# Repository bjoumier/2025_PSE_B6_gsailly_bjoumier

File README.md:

# 2025_PSE_B6_gsailly_bjoumier

### Choix Projet :

Dans le cadre de ce cours de Premier Système Embarqué, nous avons pour objectif de créer un système embarqué en ayant pour seule consigne d'y intégrer un AVR ATmega32u4 AT90USB1287 et une alimentation hybride :
- par un port USB, méthode utilisée pour la programmation, les tests et la configuration
- par une batterie Lithium, en mode autonome.

Notre binôme a donc choisi de réaliser une montre connectée qui a pour objectif principal d'afficher l'heure et de capturer les BPM de l'utilisateur. (D'autres fonctions pourront être ajoutées si elles sont réalisables)

---

### Réalisation Projet :

#### Partie Matériel :

Pour réaliser cette montre connectée, nous avons dans un premier temps utilisé le logiciel KiCad, pour réaliser le schéma et le PCB. *[(Voir /Materiel)](https://gitea.plil.fr/gsailly/2025_PSE_B6_gsailly_bjoumier/src/branch/main/Materiel)*

Suite à cette réalisation, nous avons :
- soudé le µC, le crystal et leurs capacités/résistances associées
- testé le bon fonctionnement de la carte via l'ICSP, (Comme nous n'avions pas encore le régulateur de tension et le cavalier, nous avons court-circuité la pate +5V du connecteur J8 avec R1 afin d'alimenter le µC)
- soudé les LEDs, puis testé ces dernières via un simple code pour les faire clignoter :

```c
	#define F_CPU 8000000UL
		
	#include <avr/io.h>
	#include <util/delay.h>
	
	void delay(volatile uint32_t nCount) {
	    while(nCount--) {}
	}
	
	int main(void) {
	
		CLKSEL0 = 0b00010101;   // sélection de l'horloge externe
		CLKSEL1 = 0b00001111;   // minimum de 8Mhz
		CLKPR = 0b10000000;     // modification du diviseur d'horloge (CLKPCE=1)
		CLKPR = 0;              // 0 pour pas de diviseur (diviseur de 1)
	
	    DDRB |= (1 << PB4) | (1 << PB5);
	
	    while(1) {
	         // LED sur PB5 ON
	        PORTB |= (1 << PB5);
	
	        // LED sur PB4 OFF
	        PORTB &= ~(1 << PB4);
	
	        _delay_ms(500);
	
	        // Inverser
	        PORTB &= ~(1 << PB5);
	        PORTB |= (1 << PB4);
	
	        _delay_ms(500);
	    }
	}
```
- soudé le capteur de BPM MAX30102 (que nous avons probablement grillé en le soudant puis en branchant la carte avant de souder le régulateur)
- soudé tous les connecteurs manquants ainsi que le régulateur de tension et l'inductance (ce qui nous a permis de brancher l'écran I2C et le module Bluetooth HC-05)

Enfin, à la dernière séance, nous avons soudé le MAX1811 qui nous a permis de faire fonctionner la montre via le chargeur LIPO en branchant la batterie.

#### Partie Logiciel :

Pour réaliser la partie logicielle de la montre, nous avons développé le programme embarqué en C pour le microcontrôleur ATmega32U4. *[(Voir /Logiciel)](https://gitea.plil.fr/gsailly/2025_PSE_B6_gsailly_bjoumier/src/branch/main/Logiciel)*

Nous avons utilisé plusieurs bibliothèques afin de faciliter la gestion des différents périphériques :

- **U8G2** : gestion de l’écran OLED SSD1306
- **LUFA** : gestion de la communication USB
- pilotes personnalisés pour :
  - le Bluetooth HC-05
  - le capteur MAX30102
  - l’I2C
  - les timers
  - la gestion de l’heure

##### Structure du projet

```text
Logiciel/
├──	montre_connectee/
│	├── include/
│	│   └── LUFA/
│	├── lib/
│	│   └── U8g2/
│	├── src/
│	│   ├── main.c
│	│   ├── display.c
│	│   ├── display.h
│	│   ├── i2c.c
│	│   ├── i2c.h
│	│   ├── max30102.c
│	│   ├── max30102.h
│	│   ├── timekeeper.c
│	│   ├── timekeeper.h
│	│   ├── timer.c
│	│   ├── timer.h
│	│   ├── uart.c
│	│   ├── uart.h
│	│   ├── usb_comm.c
│	│   └── usb_comm.h
│	└── Makefile
```

##### Fonctionnement général

Le programme initialise :
- l’écran OLED,
- la communication Bluetooth UART,
- les timers,
- la gestion du temps,
- ainsi que le capteur cardiaque MAX30102.

L’heure peut être synchronisée via Bluetooth grâce à l’application **Serial Bluetooth Terminal** sur tablette ou smartphone.

Un message au format suivant est envoyé :
```text
T14:30:00
```

Le microcontrôleur lit ensuite cette trame et met à jour l’horloge affichée à l’écran.

##### Affichage

L’écran affiche :
- l’heure actuelle,
- le rythme cardiaque en BPM (le capteur étant grillé, nous avons chois d'afficher une valeur de 80 BPM fixe),
- ainsi qu’une interface graphique réalisée avec la bibliothèque U8G2.

##### Communication Bluetooth

Le module **HC-05** communique avec l’ATmega32U4 via l’UART à 9600 bauds.

La réception Bluetooth est gérée directement dans la boucle principale du programme.

##### Capteur cardiaque

Le capteur **MAX30102** communique via le protocole I2C.

Nous avons développé un pilote permettant :
- l’initialisation du capteur,
- la lecture des valeurs IR,
- ainsi que le calcul du rythme cardiaque.

##### Compilation

Le projet est compilé avec `avr-gcc` via un `Makefile`.

Effacer :
```bash
make clean
```

Compilation :
```bash
make all
```

Appuer sur les boutons NHWB (maintenir) et RESET (1 pression) puis relâcher NHWB pour pouvoir re-flasher la carte.

Téléversement :
```bash
make upload
```

Débrancher puis Rebrancher la carte.

### Carte en fontionnement (USB et LIPO)

---

### Erreurs / Points d'amélioration :

#### Erreurs : 

- Mauvaise empreinte pour le crystal (empreinte légèrement trop petite).
- Nous avons voulu tester le capteur de BPM  avant d'avoir le régulateur de tension, ce qui a pu le griller (en plus de l'avoir soudé à une température trop élevée).

- Nous avions utilisé un mauvais baudrate (115200 au lieu de 9600), ce qui nous a fait perdre entre 30 et 45 minutes.
- Mauvais paramétrage de l'horloge qui prenait 8 secondes à réaliser une instruction d'1 seconde, ce qui nous a fait perdre entre 15 et 30 minutes. Nous avons résolu ce problème grâce aux 4 lignes de code fournies dans le cours de Mr Redon ainsi qu'en remplaçant le chiffre 16 (MHz) par 8 (MHz) dans le code ```uart.c``` : 

```c
CLKSEL0 = 0b00010101;   // sélection de l'horloge externe
CLKSEL1 = 0b00001111;   // minimum de 8Mhz
CLKPR = 0b10000000;     // modification du diviseur d'horloge (CLKPCE=1)
CLKPR = 0;              // 0 pour pas de diviseur (diviseur de 1)
```

```c
uint16_t ubrr = (F_CPU / 8 / baud) - 1;
```

#### Points d'amélioration :

- Utilisation d'un levier/interrupteur pour passer de l'alimentation USB à l'alimentaion sur batterie.
- Allumer la LED D4 qui indique le passage de la carte à l'alimentaion sur batterie.
- Ajouter des boutons sur la carte qui auraient permis de régler l'heure directement dessus (1 pression rajoute +1 à l'heure ou aux minutes ou aux secondes).
- Ajouter un sorte de "joystick" qui aurait pu servir à modifier l'heure (déplacement gauche pour reculer, déplacement droit pour avancer, déplacement haut pour passer à l'unité suivante, déplacement vers le bas pour passer à l'unité précédente).
- Ajouter une molette pour régler l'heure.

---

Premier Système Embarqué - IoT 3 - B6 - **[Notre Wiki](https://projets-se.plil.fr/mediawiki/index.php/SE3Groupe2025-6)** - *[Accès à notre machine de TP (zabeth16)](https://vnc.plil.fr/ssh/?16)*

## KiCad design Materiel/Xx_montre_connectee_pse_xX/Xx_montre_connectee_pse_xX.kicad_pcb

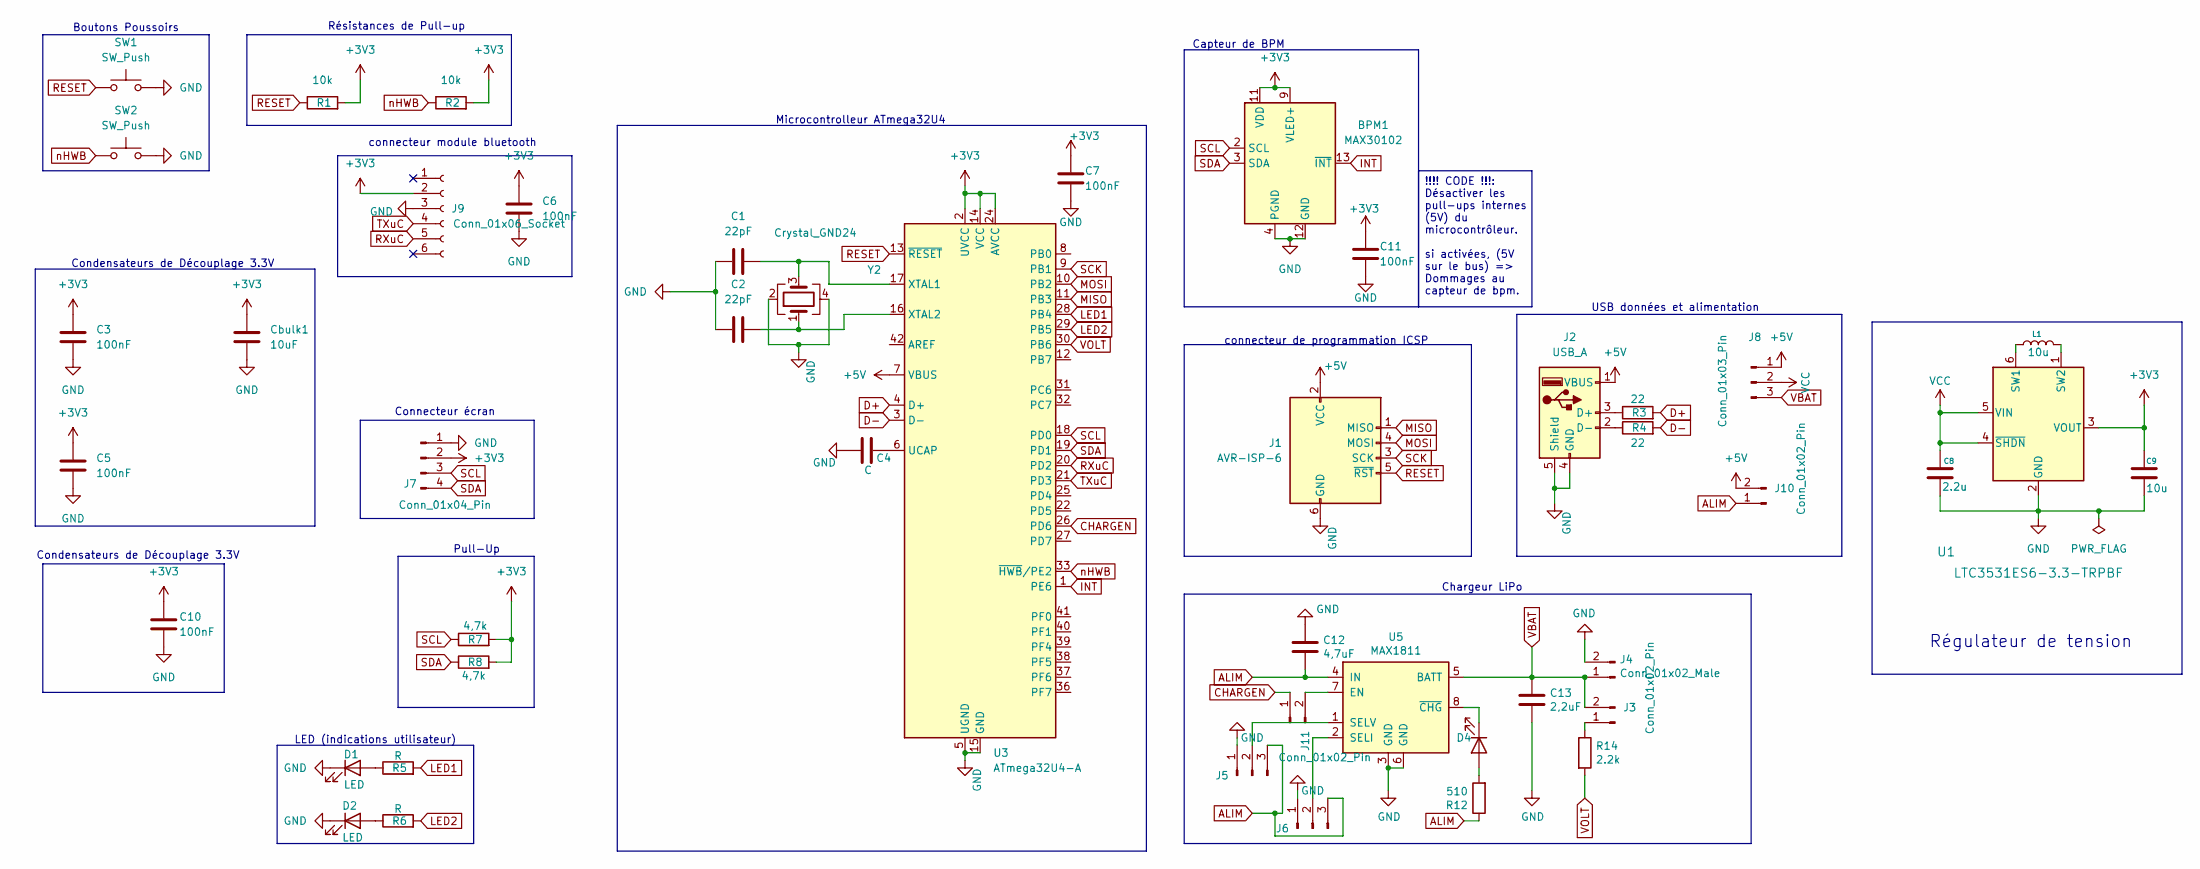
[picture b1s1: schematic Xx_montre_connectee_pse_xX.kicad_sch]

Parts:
BPM1: MAX30102; Maxim_OLGA-14_3.3x5.6mm_P0.8mm
C1, C2: 22pF; C_0603_1608Metric_Pad1.08x0.95mm_HandSolder
C3, C5, C6, C7, C10, C11: 100nF; C_0603_1608Metric_Pad1.08x0.95mm_HandSolder
C4: C; C_0603_1608Metric_Pad1.08x0.95mm_HandSolder
C8: 2.2u; C_0603_1608Metric_Pad1.08x0.95mm_HandSolder
C9: 10u; C_0603_1608Metric_Pad1.08x0.95mm_HandSolder
C12: 4,7uF; C_0603_1608Metric_Pad1.08x0.95mm_HandSolder
C13: 2,2uF; C_0603_1608Metric_Pad1.08x0.95mm_HandSolder
Cbulk1: 10uF; C_0603_1608Metric_Pad1.08x0.95mm_HandSolder
D1, D2, D4: LED; LED_0603_1608Metric_Pad1.05x0.95mm_HandSolder
J1: AVR-ISP-6; PinHeader_2x03_P2.54mm_Vertical
J2: USB_A; USB_A_CNCTech_1001-011-01101_Horizontal
J3, J10, J11: Conn_01x02_Pin; PinHeader_1x02_P2.54mm_Vertical
J4: Conn_01x02_Male; Molex_PicoBlade_53047-0210_1x02_P1.25mm_Vertical
J5, J6: Conn_01x03_Male; PinHeader_1x03_P2.54mm_Vertical
J7: Conn_01x04_Pin; PinHeader_1x04_P2.54mm_Vertical
J8: Conn_01x03_Pin; PinHeader_1x03_P2.54mm_Vertical
J9: Conn_01x06_Socket; PinHeader_1x06_P2.54mm_Vertical
L1: 10u; IND_EPCOS_B82462G4_EPC
R1, R2: 10k; R_0603_1608Metric_Pad0.98x0.95mm_HandSolder
R3, R4: 22; R_0603_1608Metric_Pad0.98x0.95mm_HandSolder
R5, R6: R; R_0603_1608Metric_Pad0.98x0.95mm_HandSolder
R7, R8: 4,7k; R_0603_1608Metric_Pad0.98x0.95mm_HandSolder
R12: 510; R_0603_1608Metric_Pad0.98x0.95mm_HandSolder
R14: 2.2k; R_0603_1608Metric_Pad0.98x0.95mm_HandSolder
SW1, SW2: SW_Push; SW_SPST_TL3342
U1: LTC3531ES6-3.3-TRPBF; TSOT-23_S6_LIT
U3: ATmega32U4-A; TQFP-44_10x10mm_P0.8mm
U5: MAX1811; SOIC-8_3.9x4.9mm_P1.27mm
Y2: Crystal_GND24; Crystal_SMD_0603-4Pin_6.0x3.5mm_HandSoldering

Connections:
+3V3: BPM1.9 (VLED+), BPM1.10 (VLED+), BPM1.11 (VDD), C3.1, C5.1, C6.1, C7.1, C9.2, C10.1, C11.1, Cbulk1.1, J7.2, J9.2, R1.2, R2.2, R7.2, R8.2, U1.3 (VOUT), U3.2 (UVCC), U3.14 (VCC), U3.24 (AVCC), U3.34 (VCC), U3.44 (AVCC)
+5V: J1.2 (VCC), J2.1 (VBUS), J8.1, J10.2, U3.7 (VBUS)
ALIM: C12.2, J5.3, J6.3, J10.1, R12.1, U5.4 (IN)
CHARGEN: J11.1, U3.26 (PD6)
D+: R3.2, U3.4 (D+)
D-: R4.2, U3.3 (D-)
GND: BPM1.4 (PGND), BPM1.12 (GND), C1.1, C2.1, C3.2, C4.2, C5.2, C6.2, C7.2, C8.1, C9.1, C10.2, C11.2, C12.1, C13.2, Cbulk1.2, D1.1 (K), D2.1 (K), J1.6 (GND), J2.4 (GND), J2.5 (Shield), J4.2, J5.1, J6.1, J7.1, J9.3, SW1.2, SW2.2, U1.2 (GND), U3.5 (UGND), U3.15 (GND), U3.23 (GND), U3.35 (GND), U3.43 (GND), U5.3 (GND), U5.6 (GND), Y2.2, Y2.4
INT: BPM1.13 (~INT), U3.1 (PE6)
LED1: R5.2, U3.28 (PB4)
LED2: R6.2, U3.29 (PB5)
MISO: J1.1 (MISO), U3.11 (PB3)
MOSI: J1.4 (MOSI), U3.10 (PB2)
unnamed: D1.2 (A), R5.1
unnamed: D2.2 (A), R6.1
unnamed: D4.2 (A), R12.2
unnamed: D4.1 (K), U5.8 (~CHG)
unnamed: J2.3 (D+), R3.1
unnamed: J2.2 (D-), R4.1
unnamed: J3.1, R14.1
unnamed: J5.2, U5.1 (SELV)
unnamed: J6.2, U5.2 (SELI)
unnamed: J11.2, U5.7 (EN)
unnamed: L1.1, U1.6 (SW1)
unnamed: L1.2, U1.1 (SW2)
unnamed: C4.1, U3.6 (UCAP)
unnamed: C1.2, U3.17 (XTAL1), Y2.3
unnamed: C2.2, U3.16 (XTAL2), Y2.1
RESET: J1.5 (~RST), R1.1, SW1.1, U3.13 (~RESET)
RXuC: J9.5, U3.20 (PD2)
SCK: J1.3 (SCK), U3.9 (PB1)
SCL: BPM1.2 (SCL), J7.3, R7.1, U3.18 (PD0)
SDA: BPM1.3 (SDA), J7.4, R8.1, U3.19 (PD1)
TXuC: J9.4, U3.21 (PD3)
VBAT: C13.1, J3.2, J4.1, J8.3, U5.5 (BATT)
VCC: C8.2, J8.2, U1.4 (~SHDN), U1.5 (VIN)
VOLT: R14.2, U3.30 (PB6)
nHWB: R2.1, SW2.1, U3.33 (~HWB/PE2)

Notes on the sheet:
Chargeur LiPo
Pull-Up
connecteur module bluetooth
Connecteur écran
connecteur de programmation ICSP
Condensateurs de Découplage 3.3V
Résistances de Pull-up
Boutons Poussoirs
Capteur de BPM
Régulateur de tension
USB données et alimentation
LED (indications utilisateur)
Microcontrolleur ATmega32U4
!!!! CODE !!!: Désactiver les pull-ups internes (5V) du microcontrôleur. si activées, (5V sur le bus) => Dommages au capteur de bpm.

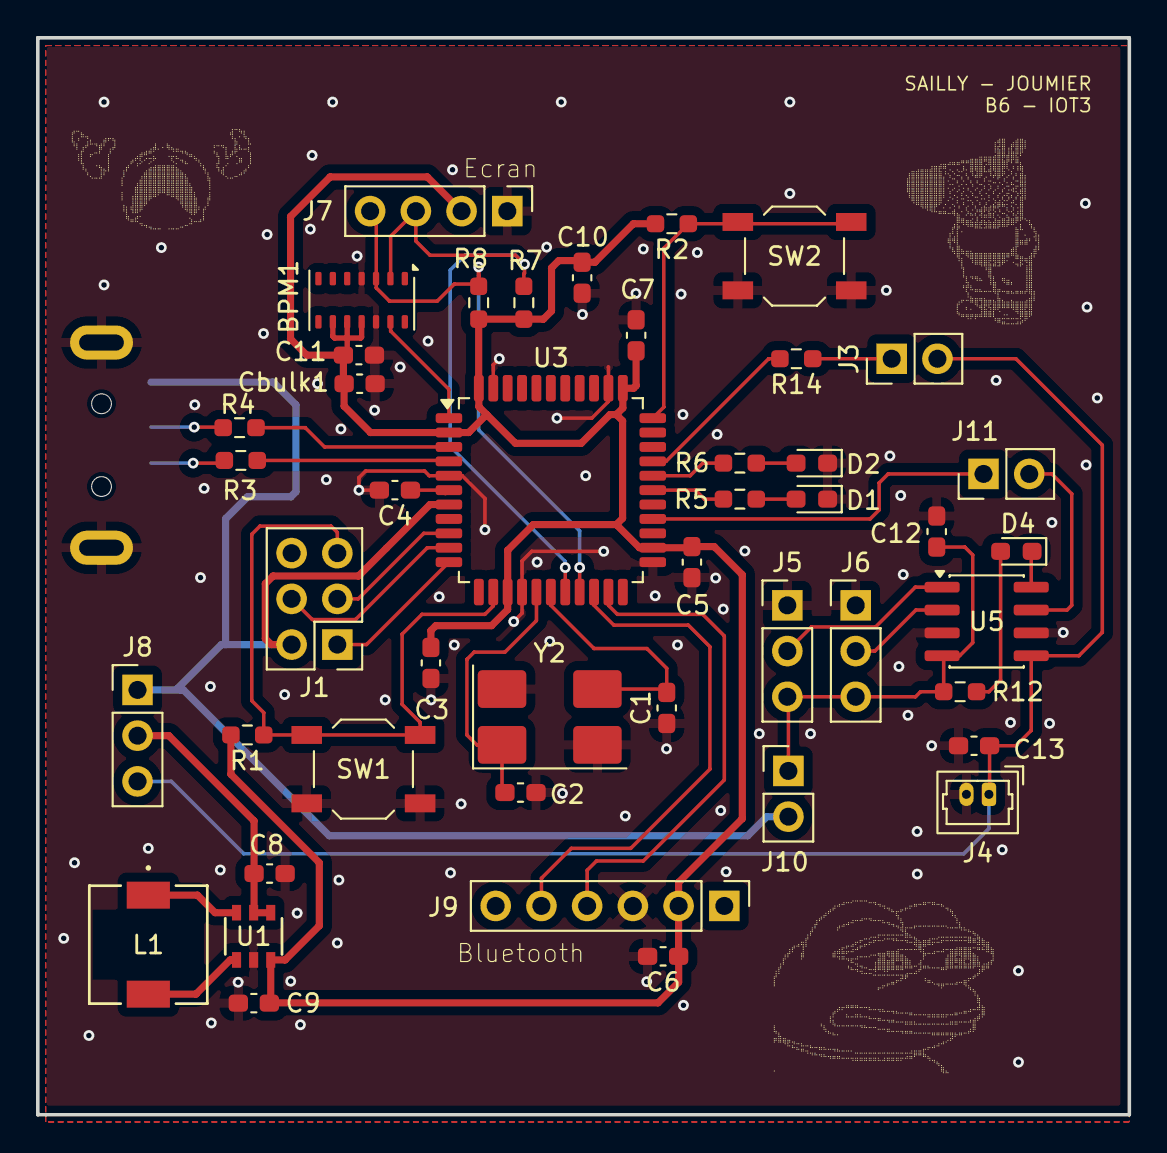
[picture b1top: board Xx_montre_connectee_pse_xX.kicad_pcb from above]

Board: 2 copper layers, 60.6 x 59.8 mm, 46 parts (1 on the bottom side), 37 nets.
